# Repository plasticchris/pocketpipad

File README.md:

# pocketpipad

gamepad PCB design for https://learn.adafruit.com/pocket-pigrrl

untested, fitted in CAD

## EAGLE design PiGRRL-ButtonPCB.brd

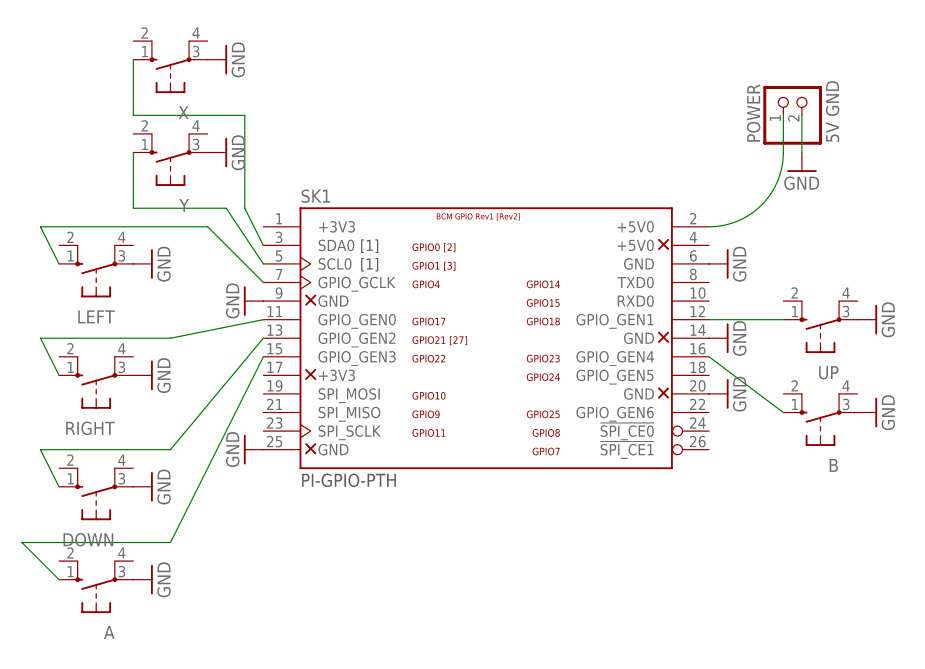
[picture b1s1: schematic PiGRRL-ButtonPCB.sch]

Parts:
A: 10-XX; B3F-10XX
B: 10-XX; B3F-10XX
DOWN: 10-XX; B3F-10XX
LEFT: 10-XX; B3F-10XX
POWER: 5V GND; 1X02
RIGHT: 10-XX; B3F-10XX
SK1: PI-GPIO-PTH; GPIO-CONNECTOR
UP: 10-XX; B3F-10XX
X: 10-XX; B3F-10XX
Y: 10-XX; B3F-10XX

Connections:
+3V3: SK1.1 (+3V3)
GND: A.3, B.3, DOWN.3, LEFT.3, POWER.2, RIGHT.3, SK1.6 (GND), SK1.9 (GND), SK1.14 (GND), SK1.20 (GND), SK1.25 (GND), UP.3, X.3, Y.3
unnamed: LEFT.1 (S), SK1.7 (GPIO_GCLK)
unnamed: RIGHT.1 (S), SK1.11 (GPIO_GEN0)
unnamed: SK1.12 (GPIO_GEN1), UP.1 (S)
unnamed: DOWN.1 (S), SK1.13 (GPIO_GEN2)
unnamed: A.1 (S), SK1.15 (GPIO_GEN3)
unnamed: B.1 (S), SK1.16 (GPIO_GEN4)
unnamed: SK1.5 (SCL0), Y.1 (S)
unnamed: SK1.3 (SDA0), X.1 (S)
unnamed: POWER.1, SK1.2 (+5V0)

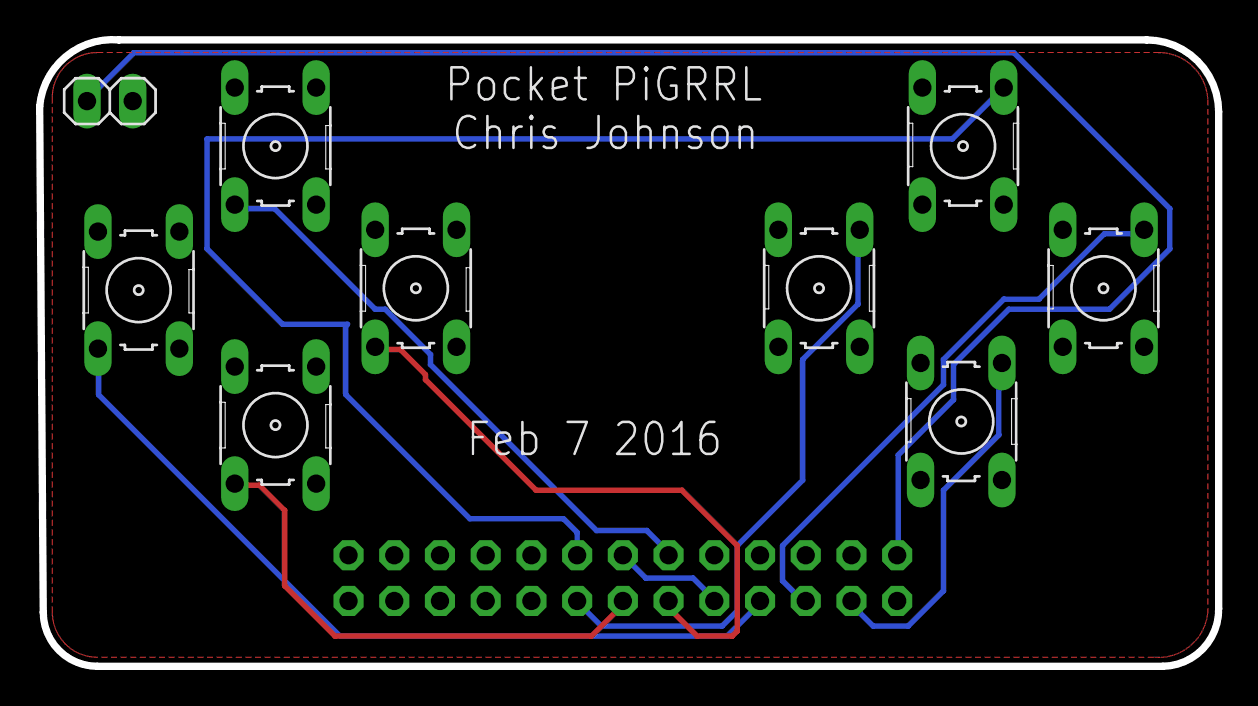
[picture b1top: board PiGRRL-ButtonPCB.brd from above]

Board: 2 copper layers, 65.5 x 34.8 mm, 10 parts (1 on the bottom side), 10 nets.

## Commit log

2016-02-08 first rev
